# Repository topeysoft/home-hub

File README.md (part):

# home-hub

A smart home hub built on the principle **own the experience and the intelligence, rent the drivers**.
Plan of record: https://claude.ai/code/artifact/cc81890a-a928-4c6f-a65d-7844fe67fbcb

## For the person receiving one

1. Plug the hub into power and the router (or its Wi‑Fi). Wait two minutes.
2. On a phone or tablet on the same Wi‑Fi, open **http://hub.local**.
3. Answer the questions on the screen: your name, where home is, which rooms, what to add.

That is the whole setup. Devices already on the Wi‑Fi (TVs, speakers, bridges) are noticed on
their own and offered under *Found nearby*; anything else is added by brand from the same screen.
Things that live behind an account (Nest, Ring, Tesla) sign in from that screen too. A few, Google's
Nest first among them, make every home bring its own key; the screen walks through getting one, with
the exact address to paste and a copy button, and the maker's own steps follow one at a time. The key
file Google hands out can be dropped or pasted straight onto that screen instead of copying its parts.
Zigbee, Z‑Wave and Matter devices pair from the same screen: the hub opens its door and says what to press.
Things that don't know their room wait under *New devices* until you place them; each arrives with a
suggested name and room and one *Use* button. Names there are whatever the driver called them
("Brilliant switch 000a", "Wiz RGBW Tunable ABC123"), so every row also says what account brought it
in and which model it is, and offers to blink it: the house flashes that one thing three times and
puts it back exactly as it found it, so you can stand in the room and see which row you are naming.
Go the other way round for anything within reach — press a switch on the wall and its row says so. A box at the top of Home takes plain words: *kitchen lights off*,
*movie in the den*, *is the front door locked?*. Simple sentences run at once, the way a tap does; anything else
goes to the assistant, which proposes and waits for your tap. The Done screen and *This hub* show a code a
phone's camera opens the house from, with the steps to put it on the phone's home screen. Once the house has a
code, only the phones it has let in can run it: a new phone asks from its own screen, someone at the wall taps
*Allow* for today, the weekend or for good, and every phone is listed under *This hub* with one *Remove*. Nothing on the
panel ever mentions Home Assistant, entities, or YAML.

## For the person building one

Any Linux box with systemd is a hub host: a Raspberry Pi 5, an Intel NUC, a mini PC, a VM under
Proxmox, running Debian, Ubuntu, Raspberry Pi OS or Fedora. One line:

```sh
curl -fsSL https://raw.githubusercontent.com/topeysoft/home-hub/main/install.sh | sudo bash
```

`install.sh` installs Docker, names the machine `hub` (so it answers at `hub.local`), writes
`driver-layer/.env`, pulls the brain image (CI publishes it for amd64 and arm64; it is built locally
only if the pull fails), and starts everything with Docker Compose. Radio sticks can be plugged in
before or after: `driver-layer/radios.sh` finds them, and a udev rule reruns it whenever one is
plugged in or pulled. Radios on the network (an Ethernet Zigbee coordinator, a PoE Z-Wave dongle)
go in `.env` as `ZIGBEE_NET` / `ZWAVE_NET` and the host needs no USB at all. The brain creates its
own login to the driver layer during the on-screen setup and adds MQTT, Z-Wave and Matter to it by
itself, so there is no token to copy and no Home Assistant UI to visit.

A flashed image rather than an install runs `driver-layer/host/firstboot.sh` once through
`home-hub-firstboot.service`: everything Pi-specific (bootloader, PCIe for an NVMe base, copying
itself from SD to an empty NVMe) happens there, then the install script. That image is built by CI on
every version tag and attached to the release as `home-hub-<tag>-hub.img.xz`: flash it with Raspberry
Pi Imager (*Use custom*), insert, power, wait, open `http://hub.local`. See `driver-layer/host/pi-image/`.
The steps below get a Pi to the same place by hand.

macOS is for developing, not for running the house: Docker Desktop cannot hand USB sticks to
containers, cannot pass multicast (so no mDNS discovery), and needs someone logged in. See
*Developing on the Mac* below.

### Getting a Pi 5 to that point

1. In Raspberry Pi Imager pick Raspberry Pi OS Lite (64-bit). In its settings set the hostname to
   `hub`, your user and SSH key, the timezone, and Wi‑Fi only as a fallback; Ethernet is what a hub wants.
2. Flash the NVMe SSD directly if you have a USB enclosure, otherwise the SD card. A third-party NVMe
   base needs `dtparam=pciex1` in `config.txt` on the boot partition; the official M.2 HAT+ does not.
3. Boot with no SD card inserted to boot from NVMe. If it does not, boot the SD card once, run
   `sudo rpi-eeprom-update -a`, set NVMe first under Advanced Options → Boot Order in `raspi-config`,
   and clone the card to the SSD with `rpi-clone`.
4. `sudo apt update && sudo apt full-upgrade -y && sudo rpi-eeprom-update -a && sudo reboot`, then
   the one line above.

Sticks go in the USB 2 ports on a short extension cable; USB 3 and the NVMe are noisy neighbors for
Zigbee in particular. Moving from a Mac that ran the stack: copy `driver-layer/ring-mqtt/` across
first to skip Ring's sign-in, do not copy `driver-layer/homeassistant/`, and stop the Mac's ring-mqtt
container before the Pi's first start so the two do not fight over Ring's token.

## Layout

- `tools/dev.sh` — the first command to run in a clone, and the one to run after a break: what this
  is and what to run, or where you left it, and then the panel on a mock house. Nothing below needs
  to be installed by hand.
- `install.sh` — the one-command install for the hub host. `driver-layer/radios.sh` finds the Zigbee and
  Z-Wave sticks and starts their containers; a udev rule runs it again whenever a stick is plugged in or pulled.
- `driver-layer/` — Docker Compose for the whole hub: Home Assistant Core (headless), Mosquitto,
  Zigbee2MQTT and Z‑Wave JS UI (profiles, on only when a stick is found), python-matter-server,
  the brain, the Matter bridge, and Caddy as the front door (`http://hub.local`, plus `https://` for those who install
  the root certificate).
- `brain/` — Python/FastAPI service on :8300: semantic home model, room-state intent engine, event
  log, websocket stream, first-run setup, device discovery. Talks only to HA's websocket and REST.
  Serves `app/dist`. `brain/Dockerfile` packages it with the panel built in.
- `app/` — Vue PWA for the wall kiosk and phone (`npm run build` → served by the brain).
- `design/` — the artboards: what a screen should look like, drawn at the size of the real display,
  before it is code. One directory per area, each with a `canvas.json` placing every board and the
  note that argues it. `tools/dev.sh design` opens the lot in a browser, on the canvas they were
  drawn on. A UI change starts here — see [`AGENTS.md`](AGENTS.md#1-a-screen-is-drawn-before-it-is-built).
- Boards and enclosures — the puck, the wall panel and their studies — live in a separate, private
  repository, [`topeysoft/home-hub-hardware`](https://github.com/topeysoft/home-hub-hardware). Every
  hub clones this one, and no house needs megabytes of board files. Its README says how to view the
  wall boards here through `design/wall`, which this repository ignores.
- `matter-bridge/` — the house as Apple Home, Google Home and Alexa see it: a Matter bridge (matter.js on Node)
  with one endpoint per shared thing, so this house's lights and plugs become Matter devices in those apps. It
  decides nothing — `brain/hub/share.py` hands it the list, and the rules about what may leave the house have tests
  there. Nothing is shared until the panel's switch is thrown (*Share this house*, its own door), and until then it
  announces nothing at all. `docs/matter.md`, `design/share/`, `matter-bridge/README.md`.
- `kiosk/` — the wall's home screen: a small Android launcher that boots into the panel, stays awake and
  full screen, finds the hub over mDNS when `hub.local` will not resolve, and has one way out (the clock's
  corner, held). It draws no house of its own; the panel comes from the hub. `kiosk/README.md`.
- The command box: `POST /say` runs `brain/hub/commands.py`, a fixed grammar over the house's own names (rooms and their
  usual other names, devices, kinds, scenes, sounds) that executes at once and deterministically. What it cannot place
  goes to the assistant, which only proposes. Every sentence is logged as a `said` event, understood or not, so the
  grammar grows from what people actually say. The microphone comes later: `docs/voice.md`.
- New devices: `GET /suggestions` (`brain/hub/suggest.py`) proposes a plain name and a room for each unplaced thing, from
  the words in its name and its hardware first, then from the assistant for whatever is still unplaced. Nothing moves
  until *Use*; that goes through the same guarded move and rename routes as doing it by hand. Telling one row from
  another is two halves that meet in the middle: a press on a wall lights its row (`app/src/pressed.ts`), and
  `POST /devices/{id}/identify` blinks a light, plug or fan three times and restores it, brightness and all, for
  everything nobody can reach. What each row knows besides its name — the account, the model — is `app/src/telling.ts`.
- Phones: once a code is set, every request needs a phone cookie (`brain/hub/phones.py`, `phones.json` in the data
  directory, hashes only). The screen that sets the first code is paired on the spot; a phone types the code
  (`POST /phones/code`) or asks (`POST /phones/ask`, polling `GET /phones/claim/{id}`) and a paired screen allows it
  behind the code (`POST /phones/asks/{id}/allow`, for a day, a weekend or to keep). `GET /phones` lists them, `DELETE`
  removes one at once. Every phone starts home-only; `remote` waits for the relay. The plan: `docs/away.md`.
- The driver layer is pinned. Every image in `driver-layer/docker-compose.yml` names the release this code was tested
  against (Home Assistant 2026.9.1, Zigbee2MQTT 2.14.1, Z-Wave JS UI 11.23.0, Matter server 8.1.2, ring-mqtt 5.9.3).
  Bumping one is a commit, so it rides the hub's own update and a breaking upstream release never reaches a house unread.
- Updates: the brain knows which build it is and checks GitHub's main a few times a day. When it has moved on, Home
  shows *An update is ready*; one tap (behind the settings code) writes `brain-data/update.request`, a systemd path
  unit on the host runs `install.sh` again, and the panel comes back on the new build. `driver-layer/host/update.sh`.
  **An update that does not come back is undone by the hub itself.** Before anything moves, where it was — the commit
  and the image the brain container is actually running — goes into `brain-data/update.prev`; afterwards the brain has
  to answer on `127.0.0.1:8300/alive` and keep answering, or the old commit and the old image go back and the version
  that did it is named in `update.json`. Home then stops offering that version on its own; the button under *This hub*
  still installs it, because a person trying again is a different thing from a hub deciding to. Putting it back needs
  no network, which matters when the thing that broke was the network.
  **A hub that can check what it is installing installs it overnight, on its own**, in the small hours, at a minute
  of its own derived from its id (so ten thousand houses do not move at once) and only once nobody has asked the
  house for anything for half an hour. One switch under *This hub* turns that off and it stays off; a hub with no
  release keys waits to be asked, because updating by itself from something nothing checks is the supply-chain
  problem with the person taken out of it. An automatic install is logged as the hub's doing, not a person's.
  **What changed is on the wall the next morning**, in a house's own words: `releases/<version>.md` is written by
  hand, ships inside the image, and is refused by `tools/release-manifest.py` if it is missing or reads like a
  changelog — no filenames, no containers, no commit subjects, and never Home Assistant. The card opens *This hub*,
  where the current release and every one before it that the build carries are kept.
  **A bad release is stopped without cutting another one**: `tools/channel.py hold v0.3.1` signs a small file that
  hubs check against the same keys, within half an hour and always before they install. The same file lets a release
  out to a fraction of houses first (`tools/channel.py out v0.3.2 0.1`). It can only ever withhold — there is no way
  to say *install this* — and missing, stale or unsigned means nothing is held, because the alternative would let
  anyone who can block a network freeze every hub where it stands. `docs/updates.md`.
- Health: Home has a quiet *Needs a look* list when something is off: a device offline since Tuesday, storage nearly
  full, a driver that wants signing in, an update that did not finish. `GET /health`; the words come from the brain.
  A line that can be acted on carries the way to do it, so none of them sends anyone to Home Assistant: an account whose
  sign-in ran out gets *Sign in again*, which opens the maker's own short form on the same sheet that adds things
  (`brain/hub/onboarding.py` tells the two kinds of open flow apart); something that could not start gets *Try again*.
- Sounds on a speaker: every speaker tile has White, Pink and Brown noise (the brain makes those itself) plus any audio
  file in the hub's sounds folder, with a sleep timer. Recordings in the repo's `sounds/` folder ship in the image and are
  copied into every hub's folder when missing (`tools/add-sound.sh` puts a download there in the right shape, and can push
  it to a hub over ssh at the same time); a household's own files go straight into `driver-layer/brain-data/sounds/` on
  the hub (`brain/sounds/` when running the brain on a Mac) and are never overwritten. `rain.mp3` shows up as *Rain*; MP3, WAV, OGG, M4A, FLAC and AAC work,
  and any length works: the brain prepares each file once (ffmpeg is in the image), crossfading its last three seconds into
  its first and repeating it to ten minutes, so the join is seamless and the speaker's own restart comes round rarely. The
  prepared copies live in `sounds/prepared/`; the originals are never touched. The speaker fetches the file from the hub's
  LAN address; the brain restarts it each time it ends, and a rule can put a sound on too (`"then": {"device": "<speaker>", "action": "sound", "data": {"sound": "rain", "minutes": 60}}`).
- Backup and restore: *This hub* on Home hands you one `.tar.gz` with the brain's settings and event log, the engine's
  config, the radios' keys, Ring's sign-in and the front door's certificate authority (not the engine's history
  database or any logs). It carries the house's keys, so it sits behind the settings code. Restoring, here or on a
  new hub's welcome screen, parks the file for `driver-layer/host/restore.sh`, which stops the house, unpacks, and
  starts it again with this hub's own address kept.
- The assistant (routines asked for in plain words, and "why did that happen?") needs a key for the model. Paste it into
  the panel's Routines sheet, or put `ANTHROPIC_API_KEY=` in `driver-layer/.env`. Without one the house runs exactly the same;
  only the asking is missing. The assistant writes drafts a person approves and explains from the log; it cannot touch a device.
- `tools/discover.py` — seeds a device inventory of your own house from a Mac (`docs/inventory.draft.md`, never committed).
- `docs/phase4-intelligence.md` — Phase 4 design: rules as data, the evaluator, holds, presence, the assistant's contract.
- `docs/settings.md` — Settings without a settings page: the four nouns under *This hub* (People, Accounts, Devices, This hub),
  what still forces a visit to Home Assistant's UI, and the order to close each gap so the Advanced door is never a step.
  Its *Where this stands* section is the dated ground truth for how much of that order has actually been built.
- `docs/updates.md` — Updates: what is built (the undo above), and the four pieces after it — a signed release
  manifest and images by digest, the hub updating itself at night, notes written for a house rather than a repository,
  and a hold to stop a bad release spreading. The rules each piece may not break are at the top.
- `docs/away.md` — Away from home: why no VPN and no cloud tunnel, the three pieces (pairing, a relay the maker runs, a
  real certificate per hub), what has landed, and the build and open decisions for the two that have not.
- `docs/voice.md` — The microphone: the shapes considered and what each waits on.
- `docs/matter.md` — Sharing the house outward: why Matter and not three integrations, the bridge that reads the
  brain rather than Home Assistant (so the owner's names and kinds travel), what may and may not be shared, the
  two decisions locks and alarms force, and what Apple, Google and Alexa actually do with an uncertified bridge.
- `docs/kinds.md` — Letting somebody correct a device's kind: why a lamp on a smart plug never hears "kitchen lights
  off", and the two fields that keep the fix from making it untouchable.
- `docs/apps.md` — Phone, tablet and desktop apps: why the panel already is the app, the four things a native
  shell would carry, and the one fork (the hub's certificate, or a pinned one in a shell) to settle after the relay.
- `docs/happened.md` — What happened: why the answer to "should there be a dashboard" is no and what was built
  instead. A finding is a span, not an event ("on for ten hours" is the news, and a timeline cannot show it), so
  what is still true leads with a button each and what is over reads quietly under it. Also the event log's
  retention — it was append-only and unbounded, on eMMC, riding every backup — and the one scoped rule that keeps
  a prune from resetting the clocks `health.py` and `rules.seed` read. And `who` asked, which is only ever written
  for a person.
- `docs/storage.md` — Storage: why the unit sold runs on eMMC and not NVMe (the finding, so it is not re-argued), and
  the plan for the hub to say months ahead that its storage is wearing out: the host reads the wear once a day, the
  brain turns it into one *Needs a look* line with *Back up* beside it, and *This hub* gets a Storage row.
- `docs/shipping.md` — Shipping it: why the unit to sell is a Compute Module 5 and not a Pi 5, the staged hardware path
  (Pi 5 kit, CM5 in a partner box, a custom carrier only later), radios on the network rather than USB, and the list of
  what is open on the Wi‑Fi or missing from the appliance layer before a stranger pays, with what can be done today.
- `docs/service.md` — The relay as a service: why the maker-run relay is the one part of an AGPL project that can be
  charged for honestly, what is sold (a box, a name, the bytes) and what may never be (any capability in the
  software), why the entitlement is checked at the relay and never in the hub, and how billing closed the
  name-squatting question for free.
- `tools/ha_bootstrap.py` — the old manual bootstrap; the brain's setup screen does this now.

## Starting, and starting again

One command, whether the checkout is an hour old or a month old:

```sh
tools/dev.sh          # a fresh clone: what this is, what each directory does, what to run.
                      # a checkout you have worked in: the branch, what is uncommitted, what is
                      # unpushed, what is stashed, what is still listening. Changes nothing.
tools/dev.sh up       # installs both halves, then the panel on the mock house — no hub needed
tools/dev.sh hub      # the same against a real brain, replaced with your code first
tools/dev.sh check    # what CI runs, minus the browser pass
tools/dev.sh free     # let go of a port still held from yesterday — all of them, or free 5173
```

`up` is the one to live in: `npm run dev:mock` with the install step in front of it, so a clone
that has never been built and a checkout from three weeks ago start the same way. It checks the
two floors first (**node 22+, python 3.13+**) and names the version it found, because a `python3`
that is 3.9 — which is what pyenv or conda often puts first on a Mac — builds a venv happily and
then fails in the tests in ways that read as bugs in the code.

It claims :8399 first, the way `hub` claims :8300 — a mock left running from an hour ago, or one
started by whoever else is in this checkout, otherwise ends `up` with a node stack that names
neither. Only a mock of ours is replaced, and it says whose it was; anything else on the port
is reported, and `PORT=8405 tools/dev.sh up` goes around it.

`hub` goes through `brain/dev.py`, which stops whatever hub is holding :8300 and starts yours: a
hub left running from before the break serves an older shape of `/home`, and the panel renders it
without complaint, so it reads as a panel bug.

`free` is the other half of that: the status report names anything still listening — a brain, a
vite, the artboard viewer — and `free` stops it, so `address already in use` does not send you
to an `lsof` and a `kill` aimed by hand. A port a container publishes is reported and left
alone, because that pid is docker's and killing it takes docker's networking rather than the
container.

## Developing on the Mac (until the Pi arrives)

`driver-layer/docker-compose.mac.yml` runs Home Assistant, Mosquitto and Caddy in Docker with no
radios and no host networking (Docker Desktop on macOS cannot do mDNS discovery, so devices are
added by IP or by brand). Run `driver-layer/mqtt-auth.sh` once first: Mosquitto refuses to start
without its password file, and the brain reads the same `.env` to give the engine the password.
The brain runs from its venv (`cd brain && .venv/bin/python main.py`) and
finds HA at `http://localhost:8123`. Panel: `http://localhost:8300/` (or `:8088` through Caddy).

The brain keeps what it learns in `brain/settings.json` (gitignored): the engine login it created,
the owner's and home's names, the location, whether setup finished. Delete the file to run setup
again. `driver-layer/.env` can still carry `HA_URL`/`HA_TOKEN` as a developer override.

Preview any panel state from the address bar: `?setup=1&page=rooms` (a setup screen), `?rest=1`
(the resting clock), `?sheet=add` (the add-a-device sheet), `?at=19:30`, `?wx=rainy`.

### HTTPS

Caddy fronts the brain on plain `http://hub.local` with nothing to install, and on `https://` from
its own local certificate authority. The QR code, the home-screen steps and joining a phone work over plain http; web
push and the browser microphone wait on a trusted https origin. On the LAN today that means installing
`driver-layer/caddy/data/caddy/pki/authorities/local/root.crt` on the tablet or phone once (iOS
also wants full trust on under Settings → General → About → Certificate Trust Settings), which is fine for the wall
and not something to ask of a phone. The decided way out is a public name per hub with a real certificate, reached
through a relay the maker runs when the phone is away and directly when it is home: `docs/away.md`. No VPN app, no
vendor login.

## Radios and the Advanced door

Nothing here needs a visit. The brain watches the driver layer and adds each part to Home Assistant
itself when it answers: MQTT, the Z-Wave radio (Z-Wave JS UI's settings, including its network
keys, are written once by `radios.sh`), and Matter. The panel's *Behind the scenes* list shows each
part's state; Ring is the one that needs a person, once, to sign in. Plugging a stick in later
starts its container and connects it the same way.

For the curious: Home Assistant on `:8123` is the Advanced door, linked from the bottom of the location
and add sheets, never the product. Zigbee2MQTT's and Z‑Wave JS UI's own consoles (`:8080`, `:8091`) and
the Matter server answer on the hub itself only, not on the Wi‑Fi (`ssh -L 8080:localhost:8080 hub.local`
reaches one); they have no sign-in of their own, so nothing on the network gets to pair or unpair a device
past the panel. Messages (Mosquitto, `:1883`) stays on the Wi‑Fi because a bridge on the network needs it,
and takes a password: `driver-layer/mqtt-auth.sh` makes it once into `.env`, writes the broker's password file
and Ring's config from it, compose hands it to Zigbee2MQTT, and the brain gives it to the engine. The host itself gets a watchdog and capped logs from
`driver-layer/host/harden.sh`. What is still open on the Wi‑Fi, and why, is in `docs/shipping.md`.

### Brilliant

Brilliant has no official API. Do not use the HomeKit path (pairings drop, entities stick in
setup_retry). Use the community `brilliant-mqtt` bridge instead: an MIT-licensed agent that runs on
each Control panel over the panel's own **Root SSH Login** setting and publishes every wired load,
BLE-mesh dimmer switch, plug, motion and power reading to Mosquitto. One panel is elected to bridge
the whole mesh, with failover.

1. On each Control panel: Settings → enable *Root SSH Login*, set a root password.
2. Install HACS into the HA container: `docker exec -it homeassistant bash -c "wget -O - https://get.hacs.xyz | bash -"`, restart HA, add the HACS integration.
3. HACS → custom repository `joyfulhouse/brilliant-mqtt` → install → add the integration with each panel's IP and root password.
4. Add the `mqtt` integration in HA pointing at `mosquitto:1883` if not already done.

## Hardware to order

- Pi 5 8 GB + NVMe HAT + SSD (hub host)
- Home Assistant Connect ZBT-1 (Zigbee + Thread border router)
- Zooz ZST39 (Z-Wave 800). Optional while the Nortek HUSBZB-1 on hand covers Z-Wave: it is 500-series, fine for the GE/Jasco switches, no Long Range.
- ratgdo32 (garage door, Security+ 2.0 only)

## Tests and CI

Every push, on **every branch**, and every pull request runs `.github/workflows/ci.yml` — a long-lived
branch like `panel-bento` is exactly where a regression has time to settle in unnoticed. It runs: the brain's tests and linter, the
panel's types, linter and unit tests, the built panel driven in a real browser, the shell that runs
on the hub host, and the brain's container image built for both kinds of host (built, not pushed —
so a Dockerfile that no longer works is caught before it reaches the thing `install.sh` pulls).

```sh
cd brain && .venv/bin/python -m pytest tests -q     # the hub
cd app && npm test && npm run e2e                   # the screens, then the screens in a browser
```

`npm run e2e` starts its own mock on :8399, or reuses one already running there. To point it at a
different panel — another branch's build, or a real hub — set `BASE`, and nothing is started locally:

```sh
cd .claude/worktrees/panel-bento/app && npm run build && PORT=8401 npm run mock &
cd app && BASE=http://localhost:8401 npm run e2e
```

Coverage may go up and may not go down: `.github/coverage-check.py` compares each run against
`.github/coverage-floor.json` and fails a change that leaves the codebase less covered than it found
it. There is no target to reach, and the floor is raised by hand in the change that earns it.

Two things are checked that nothing else would notice. `brain/tests/sun-positions.json` holds both
sun implementations — `brain/hub/sun.py` and `app/src/sun.ts`, the same math written twice — to one
table, so the panel's dusk and an after-dark routine cannot drift apart. And `brain/tests/test_shipped.py`
holds `rules.json` and `scenes.json` to what a house that has just been plugged in can actually run:
a starter rule may only name `home` or `entry`, because any other room is one only somebody's
particular house has, and the engine would drop it on every other hub with nothing but a log line.

## Releasing

A version tag is what ships. Nothing else does.

```sh
git tag v0.2.0 && git push --tags
# ...wait for CI to publish the images, then:
tools/release.sh v0.2.0
```

The tag runs the full test suite against the tagged commit and, only if it passes, builds two things: the
brain's container for amd64 and arm64 (tagged `0.2.0`, `0.2` and `latest`, and signed with cosign), and the
flash-and-go Pi image, attached to a GitHub release with its checksum. A tag is not a branch, so branch protection
does not cover one — the test run is what stops a release being cut from a commit that never passed.

**The first one, in order.** `tools/release.sh --check v0.3.0` says which of these is not done yet and
changes nothing, so it is the thing to run between each step:

1. **Make the GHCR package public.** Until the brain image is readable, no release can be signed at all —
   `tools/release-manifest.py` names every image by digest and cannot resolve one it cannot see. It is also what
   stops a hub in a house compiling the brain on its own processor instead of pulling it.
2. **`tools/release.sh --new-key`, then `tools/release.sh --new-key spare`,** in the same sitting. Commit both public
   halves; keep the private halves off this machine's only disk and off GitHub. A hub trusts the keys it was
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
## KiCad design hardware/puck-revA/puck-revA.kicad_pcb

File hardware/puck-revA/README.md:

## Current revision — common side switches, 26 September 2026

SW1/SW2/SW3 now use KMS221GLFS / C221698. BOOT/RESET pull-ups, C7 and the RESET series resistor have been revised. The matching manufacturing package is `manufacturing/20260926-common-switches/`. Read its `REVISION-NOTES.md`. Earlier root-level Gerber, CSV and STEP exports are superseded. Final DRC, unrouted count, schematic parity and ERC all report zero issues under the existing project rules. This does not replace the remaining prototype and firmware tests below.

# Puck rev A — current working design

Open **puck-revA.kicad_pro** in KiCad. This is the promoted pass20 design: six warm-white RGBW LEDs, four copper layers, nominal 1.6 mm thickness, and a 50 mm round board.

The KiCad schematic and routed PCB in this directory are now the authoritative editable design. Project symbols and footprints are included with project-relative library paths. Older generation scripts describe a superseded circuit and are retained only in the archived original; do not regenerate this design with those scripts.

## Status

Working design, **not approved for fabrication**. The saved pass20 DRC reports zero violations/unconnected items and the independent netlist check matches 193 pin assignments. See [validation](validation/) for the recorded reports and [remaining checks](REMAINING-CHECKS.md) for the firmware and bench-validation requirements. BOM-review.csv lists candidate parts, not an approved assembly order.

The enclosure source is preserved unchanged. Its side-button actuator height/travel, antenna installation and physical fit still require validation. The earlier B2 review flagged about 0.30 mm available travel versus up to 0.40 mm switch travel before tolerance; this promotion does not close that issue.

## Next work

- Implement the dedicated six-RGBW firmware profile and USB-C power policy.
- Confirm button/other part sourcing and USB connector assembly process.
- Validate blank-chip USB programming, current limiting, supply transients, temperatures and enclosure fit on hardware.
- Export and inspect a consistent manufacturing package after design/assembly choices are resolved. Previous Gerbers are historical and must not be used with this revision.

The promotion manifest records the original backup and intermediate-revision archive locations. No order was placed and no firmware was deployed.

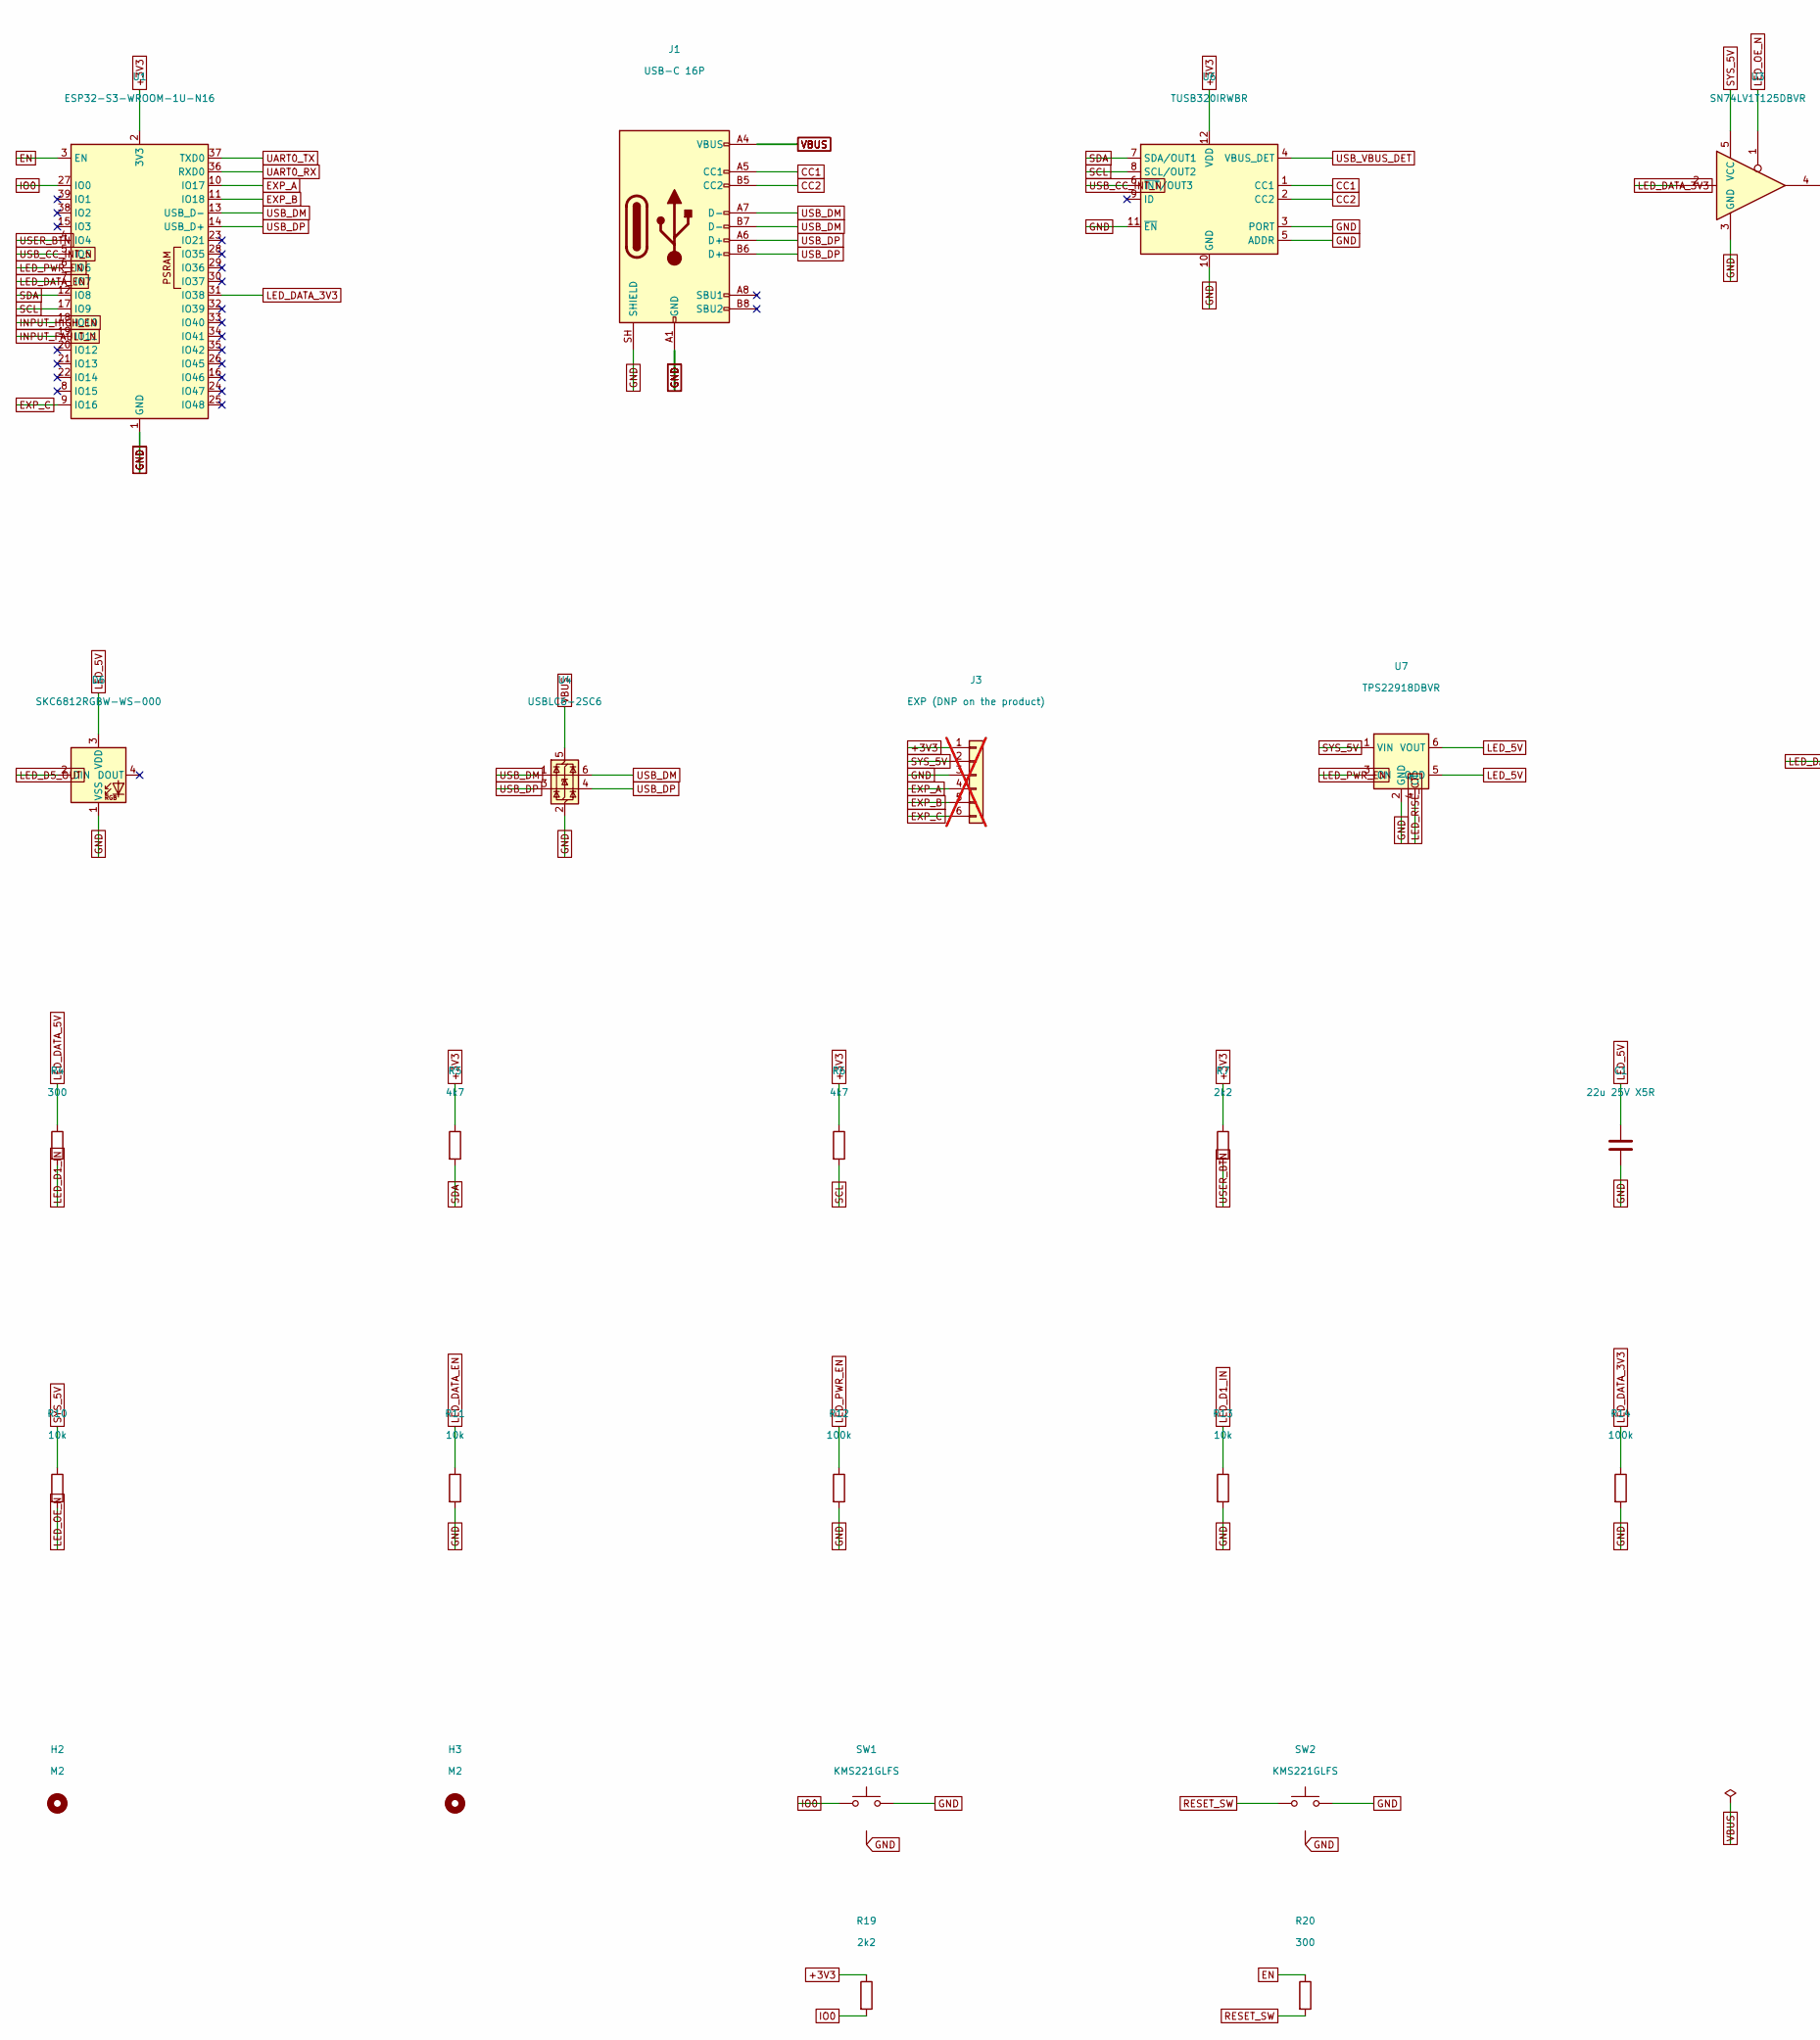
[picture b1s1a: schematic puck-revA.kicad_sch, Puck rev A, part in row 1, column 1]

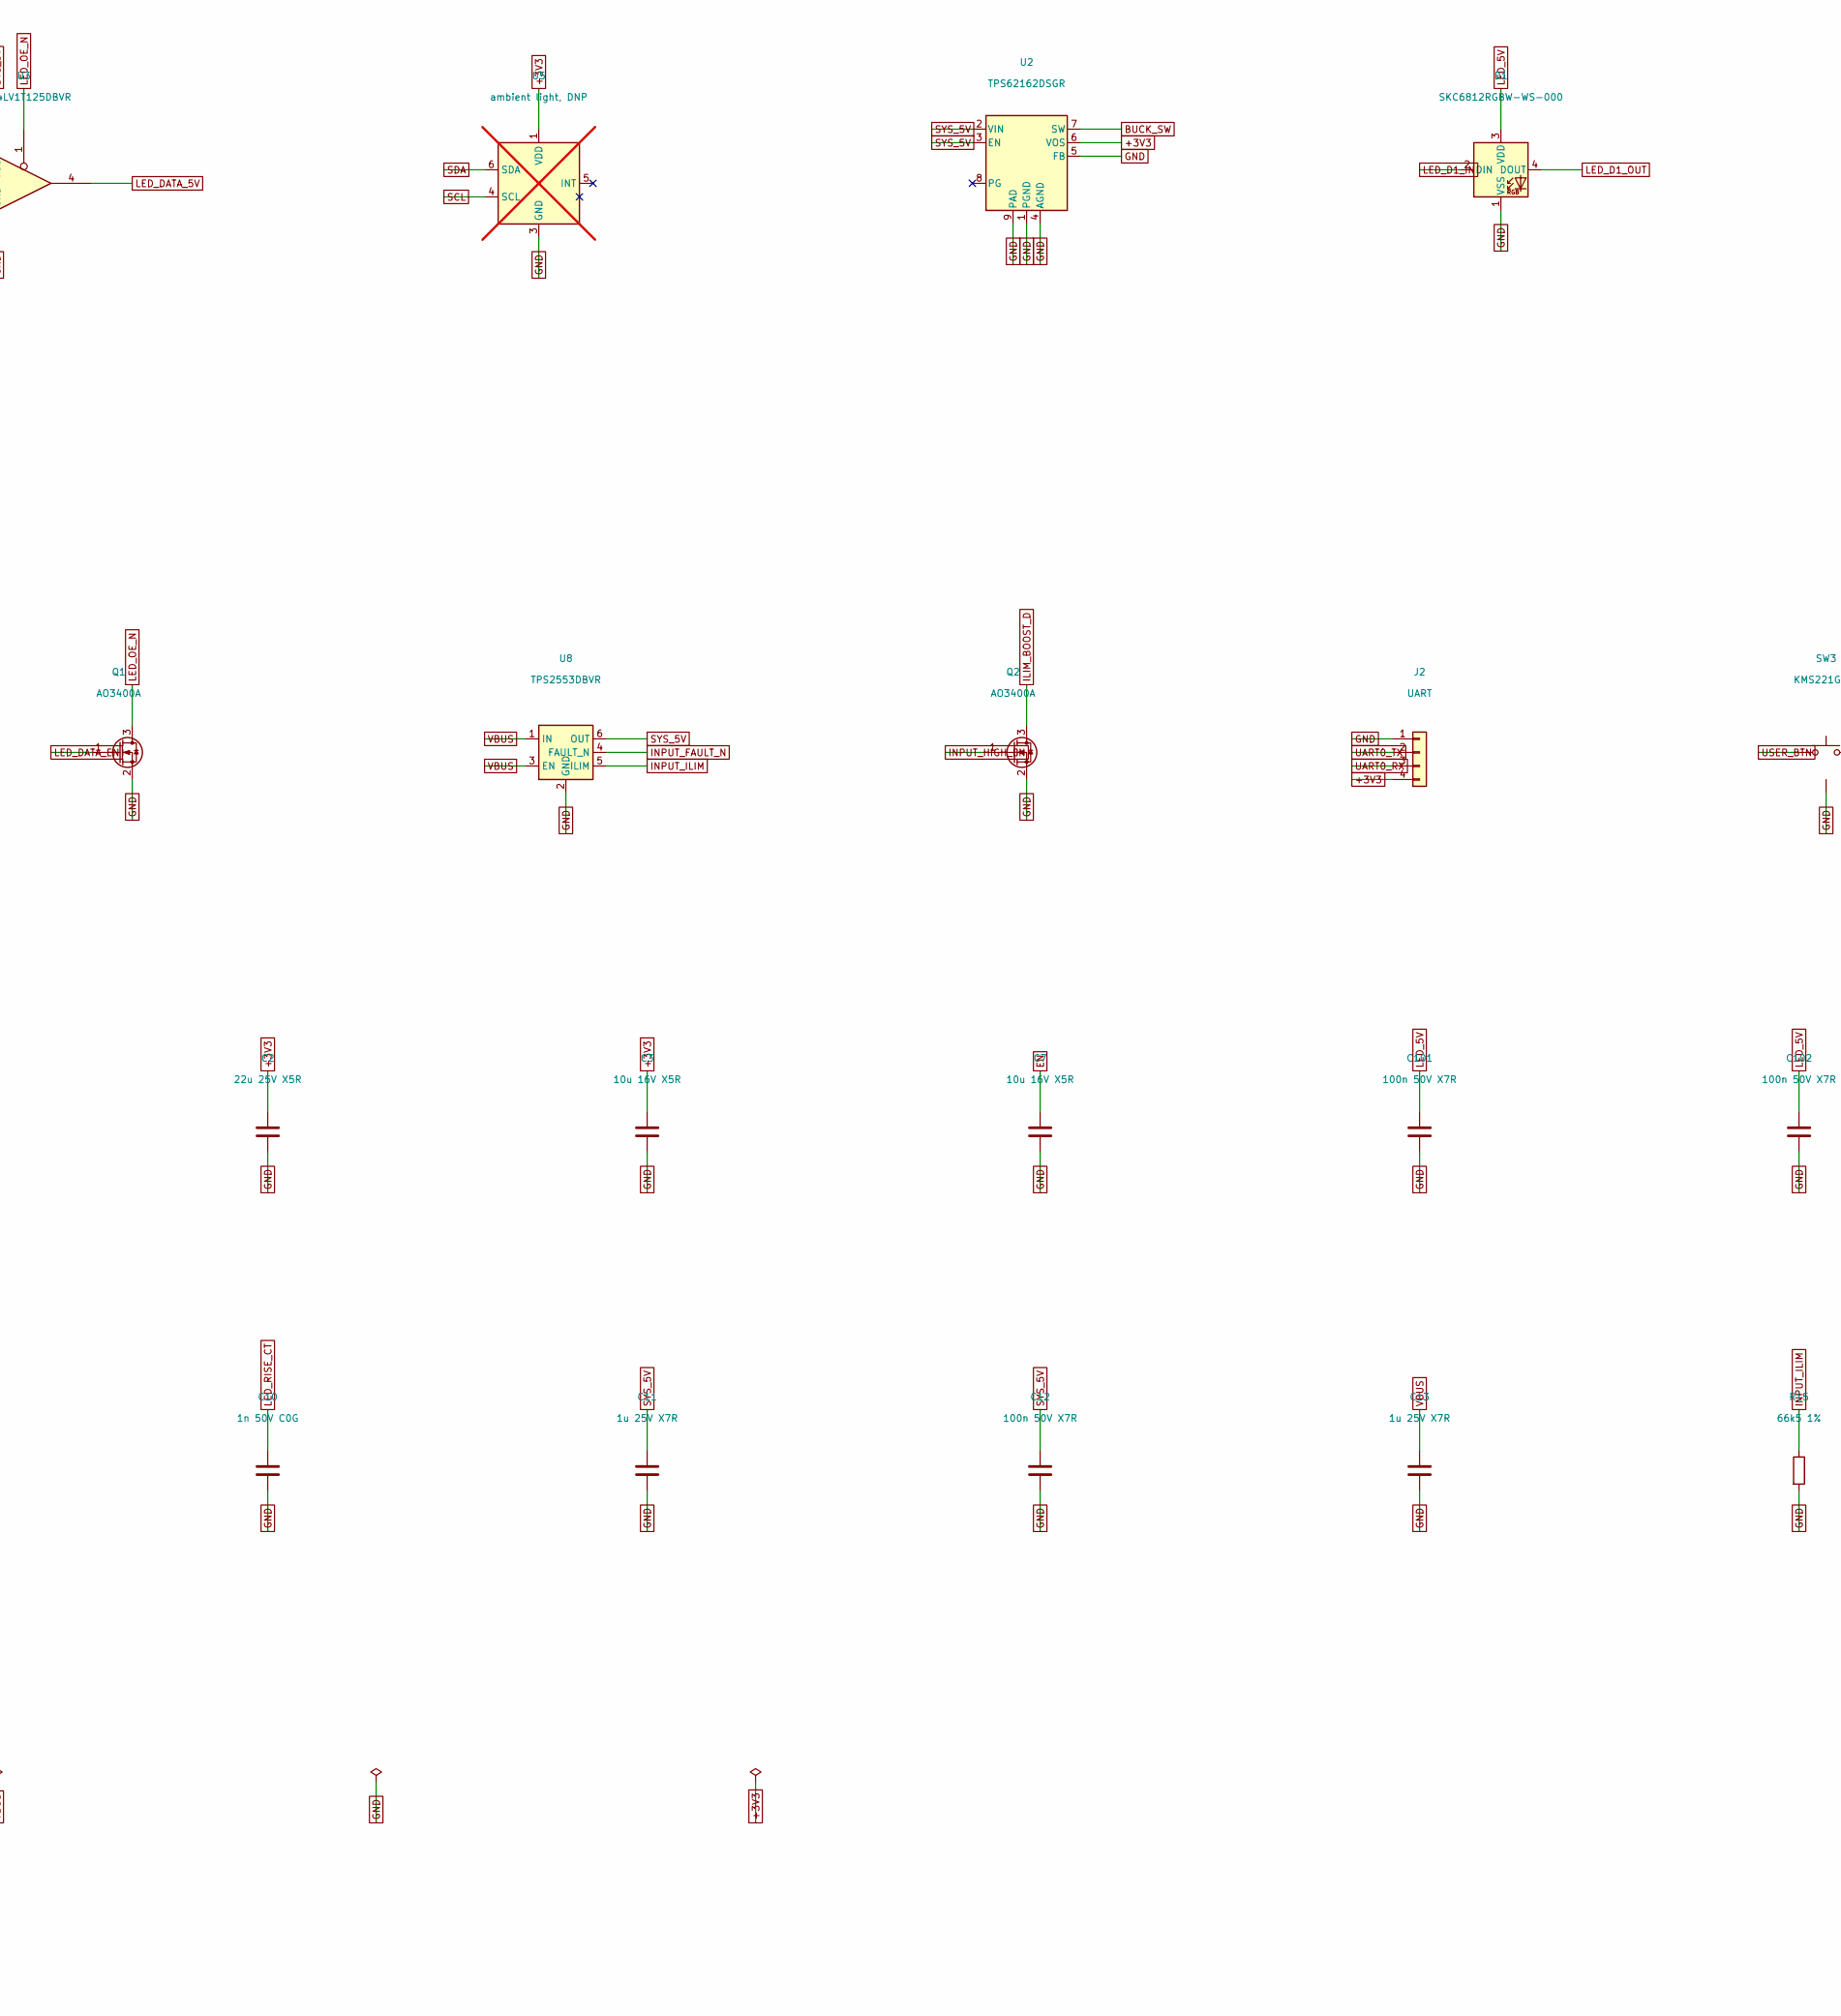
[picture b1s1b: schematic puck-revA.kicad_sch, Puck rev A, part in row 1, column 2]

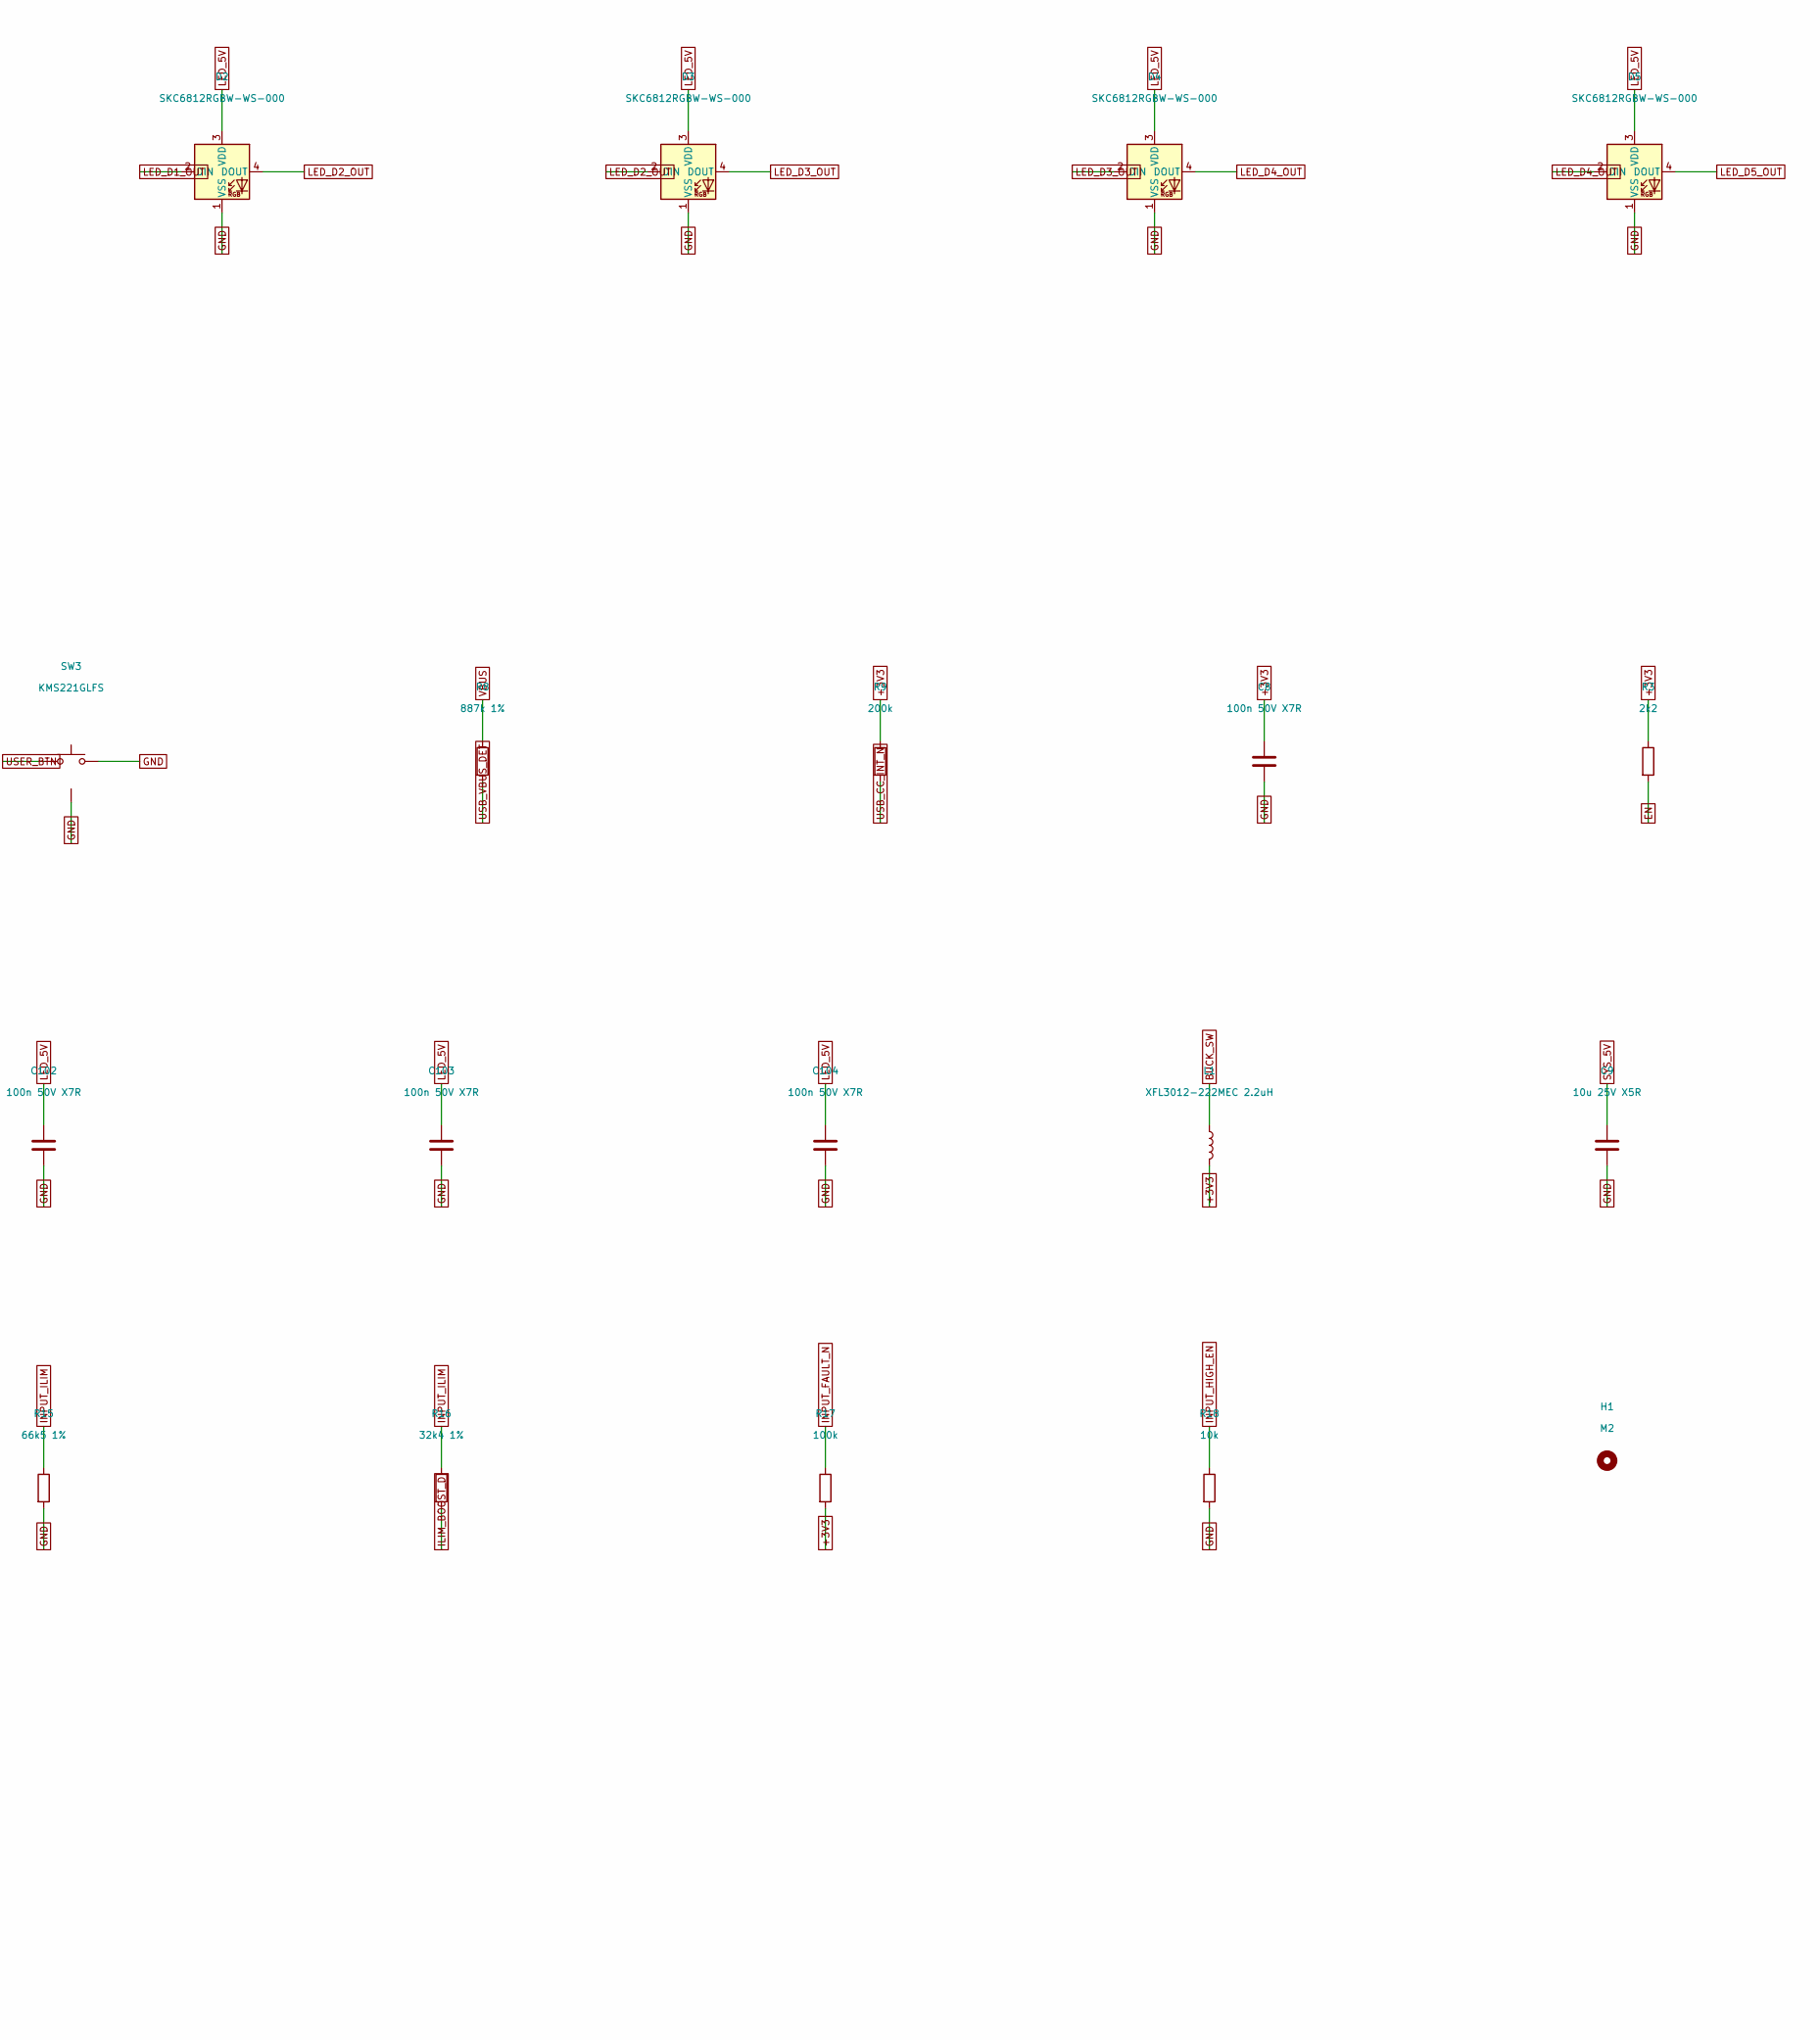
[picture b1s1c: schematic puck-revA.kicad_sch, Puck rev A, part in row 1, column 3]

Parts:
C1, C2: 22u 25V X5R; C_0805_2012Metric; MPN GRM21BR61E226ME44L; LCSC C86816
C3, C7: 10u 16V X5R; C_0603_1608Metric; MPN GRM188R61C106KAALD; LCSC C86275
C8, C12, C101, C102, C103, C104: 100n 50V X7R; C_0603_1608Metric; MPN CL10B104KB8NNNC; LCSC C1591
C9: 10u 25V X5R; C_0805_2012Metric; MPN CL21A106KAYNNNE; LCSC C15850
C10: 1n 50V C0G; C_0603_1608Metric; MPN CL10C102JB8NNNC; LCSC C163508
C11, C13: 1u 25V X7R; C_0603_1608Metric; MPN CL10B105KA8NNNC; LCSC C29936
D1, D2, D3, D4, D5, D6: SKC6812RGBW-WS-000; LED_SKC6812RGBW_WS_5050; MPN SKC6812RGBW-WS-000; LCSC C5378724
H1, H2, H3: M2; MountingHole_2.2mm_M2
J1: USB-C 16P; USB_C_Receptacle_GCT_USB4105-xx-A_16P_TopMnt_Horizontal; MPN USB4105-GF-A-120; LCSC C5184243
J2: UART; PinHeader_1x04_P1.27mm_Vertical
J3: EXP (DNP on the product); PinHeader_1x06_P1.27mm_Vertical; not fitted
L1: XFL3012-222MEC 2.2uH; L_Coilcraft_XFL3012; MPN XFL3012-222MEC; LCSC C3911432
Q1, Q2: AO3400A; SOT-23; MPN AO3400A; LCSC C20917
R3, R19: 2k2; R_0603_1608Metric; MPN 0603WAF2201T5E; LCSC C4190
R4, R20: 300; R_0603_1608Metric; MPN 0603WAF3000T5E; LCSC C23025
R5, R6: 4k7; R_0603_1608Metric; MPN 0603WAF4701T5E; LCSC C23162
R7: 2k2; R_0402_1005Metric; MPN 0402WGF2201TCE; LCSC C25879
R8: 887k 1%; R_0603_1608Metric; MPN RC0603FR-07887KL; LCSC C246015
R9: 200k; R_0603_1608Metric; MPN 0603WAF2003T5E; LCSC C25811
R10, R11, R13, R18: 10k; R_0603_1608Metric; MPN 0603WAF1002T5E; LCSC C25804
R12, R14, R17: 100k; R_0603_1608Metric; MPN 0603WAF1003T5E; LCSC C25803
R15: 66k5 1%; R_0603_1608Metric; MPN RC0603FR-0766K5L; LCSC C137691
R16: 32k4 1%; R_0603_1608Metric; MPN 0603WAF3242T5E; LCSC C13187
SW1, SW2, SW3: KMS221GLFS; SW_SPST_CK_KMS2xxG; MPN KMS221GLFS; LCSC C221698
U1: ESP32-S3-WROOM-1U-N16; ESP32-S3-WROOM-1U; MPN ESP32-S3-WROOM-1U-N16; LCSC C2980298
U2: TPS62162DSGR; Texas_DSG0008A_WSON-8-1EP_2x2mm_P0.5mm_EP0.9x1.6mm_ThermalV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; MPN TPS62162DSGR; LCSC C40256
U3: SN74LV1T125DBVR; SOT-23-5; MPN SN74LV1T125DBVR; LCSC C473338
U4: USBLC6-2SC6; SOT-23-6; MPN USBLC6-2SC6; LCSC C7519
U5: ambient light, DNP; Lite-On_LTR-303ALS-01; not fitted
U6: TUSB320IRWBR; Texas_X2QFN-12_1.6x1.6mm_P0.4mm; MPN TUSB320IRWBR; LCSC C80170
U7: TPS22918DBVR; SOT-23-6; MPN TPS22918DBVR; LCSC C131941
U8: TPS2553DBVR; SOT-23-6; MPN TPS2553DBVR; LCSC C55266

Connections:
+3V3: C2.1, C3.1, C8.1, J2.4, J3.1, L1.2, R3.1, R5.1, R6.1, R7.1, R9.1, R17.2, R19.1, U1.2 (3V3), U2.6 (VOS), U5.1 (VDD), U6.12 (VDD)
BUCK_SW: L1.1, U2.7 (SW)
CC1: J1.A5 (CC1), U6.1 (CC1)
CC2: J1.B5 (CC2), U6.2 (CC2)
EN: C7.1, R3.2, R20.1, U1.3 (EN)
EXP_A: J3.4, U1.10 (IO17)
EXP_B: J3.5, U1.11 (IO18)
EXP_C: J3.6, U1.9 (IO16)
GND: C1.2, C2.2, C3.2, C7.2, C8.2, C9.2, C10.2, C11.2, C12.2, C13.2, C101.2, C102.2, C103.2, C104.2, D1.1 (VSS), D2.1 (VSS), D3.1 (VSS), D4.1 (VSS), D5.1 (VSS), D6.1 (VSS), J1.A1 (GND), J1.A12 (GND), J1.B1 (GND), J1.B12 (GND), J1.SH (SHIELD), J2.1, J3.3, Q1.2 (S), Q2.2 (S), R11.2, R12.2, R13.2, R14.2, R15.2, R18.2, SW1.2, SW1.SH, SW2.2, SW2.SH, SW3.2, SW3.SH, U1.1 (GND), U1.40 (GND), U1.41 (GND), U2.1 (PGND), U2.4 (AGND), U2.5 (FB), U2.9 (PAD), U3.3 (GND), U4.2 (GND), U5.3 (GND), U6.3 (PORT), U6.5 (ADDR), U6.10 (GND), U6.11 (~EN), U7.2 (GND), U8.2 (GND)
ILIM_BOOST_D: Q2.3 (D), R16.2
INPUT_FAULT_N: R17.1, U1.19 (IO11), U8.4 (FAULT_N)
INPUT_HIGH_EN: Q2.1 (G), R18.1, U1.18 (IO10)
INPUT_ILIM: R15.1, R16.1, U8.5 (ILIM)
IO0: R19.2, SW1.1, U1.27 (IO0)
LED_5V: C1.1, C101.1, C102.1, C103.1, C104.1, D1.3 (VDD), D2.3 (VDD), D3.3 (VDD), D4.3 (VDD), D5.3 (VDD), D6.3 (VDD), U7.5 (QOD), U7.6 (VOUT)
LED_D1_IN: D1.2 (DIN), R4.2, R13.1
LED_D1_OUT: D1.4 (DOUT), D2.2 (DIN)
LED_D2_OUT: D2.4 (DOUT), D3.2 (DIN)
LED_D3_OUT: D3.4 (DOUT), D4.2 (DIN)
LED_D4_OUT: D4.4 (DOUT), D5.2 (DIN)
LED_D5_OUT: D5.4 (DOUT), D6.2 (DIN)
LED_DATA_3V3: R14.1, U1.31 (IO38), U3.2
LED_DATA_5V: R4.1, U3.4
LED_DATA_EN: Q1.1 (G), R11.1, U1.7 (IO7)
LED_OE_N: Q1.3 (D), R10.2, U3.1
LED_PWR_EN: R12.1, U1.6 (IO6), U7.3 (ON)
LED_RISE_CT: C10.1, U7.4 (CT)
RESET_SW: R20.2, SW2.1
SCL: R6.2, U1.17 (IO9), U5.4 (SCL), U6.8 (SCL/OUT2)
SDA: R5.2, U1.12 (IO8), U5.6 (SDA), U6.7 (SDA/OUT1)
SYS_5V: C9.1, C11.1, C12.1, J3.2, R10.1, U2.2 (VIN), U2.3 (EN), U3.5 (VCC), U7.1 (VIN), U8.6 (OUT)
UART0_RX: J2.3, U1.36 (RXD0)
UART0_TX: J2.2, U1.37 (TXD0)
USB_CC_INT_N: R9.2, U1.5 (IO5), U6.6 (~INT/OUT3)
USB_DM: J1.A7 (D-), J1.B7 (D-), U1.13 (USB_D-), U4.1 (I/O1), U4.6 (I/O1)
USB_DP: J1.A6 (D+), J1.B6 (D+), U1.14 (USB_D+), U4.3 (I/O2), U4.4 (I/O2)
USB_VBUS_DET: R8.2, U6.4 (VBUS_DET)
USER_BTN: R7.2, SW3.1, U1.4 (IO4)
VBUS: C13.1, J1.A4 (VBUS), J1.A9 (VBUS), J1.B4 (VBUS), J1.B9 (VBUS), R8.1, U4.5 (VBUS), U8.1 (IN), U8.3 (EN)

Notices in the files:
README.md:
[GNU Affero General Public License v3.0](LICENSE). Copyright 2026 Temitope Adeyeri.
Free software, in the sense that matters: run it, read it, change it, share it, sell it. The one
condition is that it stays that way — if you distribute this hub, or run a modified version as a
service other people reach over a network, those people are entitled to your source under the same
license.
The source is public on purpose, and the license is the promise behind it. A box that claims to work
with the internet down, and to keep a household's life off somebody else's servers, should be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
